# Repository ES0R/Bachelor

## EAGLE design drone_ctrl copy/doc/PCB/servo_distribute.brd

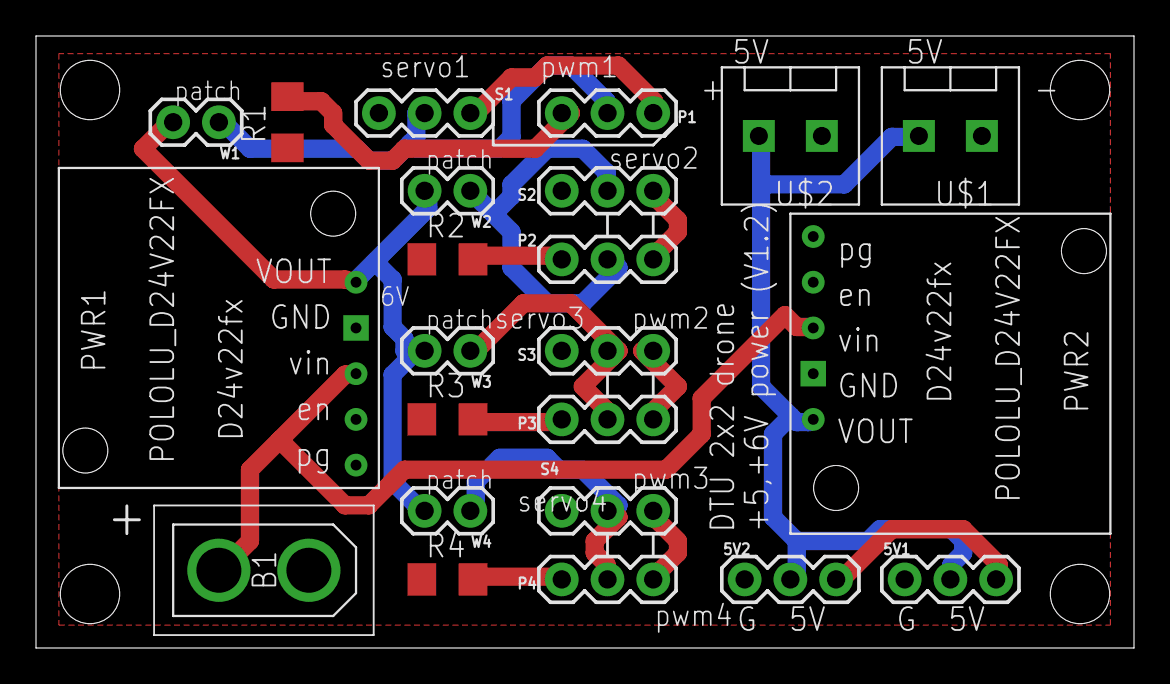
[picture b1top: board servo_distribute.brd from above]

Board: 2 copper layers, 61.0 x 34.0 mm, 23 parts (0 on the bottom side), 17 nets.

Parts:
5V1, 5V2: 1X03
B1: XT30; XT30PB
P1, P2, P3, P4: 1X03
PWR1, PWR2: POLOLU_D24V22FX; POLOLU_D24V22F6
R1, R2, R3, R4: 10; R1206
S1, S2, S3, S4: 1X03
U$1, U$2: TERMINAL_3.5MM
W1, W2, W3, W4: 1X02

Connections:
5V: 5V1.2, 5V2.2, PWR2.VOUT, U$1.F, U$2.F
6V: PWR1.VOUT, W1.2, W2.2, W3.2, W4.2
6V1: P1.2, S1.2, W1.1
6V2: P2.2, S2.2, W2.1
6V3: P3.2, S3.2, W3.1
6V4: P4.2, S4.2, W4.1
BATTERY: B1.V+, PWR1.VIN, PWR2.VIN
G1: P1.1, R1.2
G2: P2.1, R2.2
G3: P3.1, R3.2
G4: P4.1, R4.2
GND: 5V1.1, 5V2.1, B1.V-, PWR1.GND, PWR2.GND, R1.1, R2.1, R3.1, R4.1, S1.1, S2.1, S3.1, S4.1, U$1.G, U$2.G
S1: P1.3, S1.3
S2: P2.3, S2.3
S3: P3.3, S3.3
S4: P4.3, S4.3
S5: 5V1.3, 5V2.3

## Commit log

2022-02-07 Adding simulation bachelor project
2022-02-16 Added drone control files
2022-02-18 core_pins
2022-02-18 deps
2022-02-18 Please virk
2022-02-18 virk lige
2022-02-21 ustate til upload
2022-02-21 hex fil
2022-04-25 sådan cirka alt

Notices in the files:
parts and their libraries:
SparkFun-Connectors: Licensing: Creative Commons ShareAlike 4.0 International - https://creativecommons.org/licenses/by-sa/4.0
